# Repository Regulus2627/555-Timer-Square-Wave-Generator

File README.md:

555 Timer Square Wave Generator

This project implements an **Astable Multivibrator using the NE555 Timer IC** to generate a stable square wave. It was designed, simulated in **LTspice**, and built on a **PCB**.

Objectives

- **Frequency:** ~650 Hz  
- **Duty Cycle:** ~65%  
- **Tools Used:** LTspice + EasyEDA PCB  

## Circuit Details

The 555 timer operates in **Astable Mode**, continuously switching between HIGH and LOW.

**Components:**
- R1 = 12 kΩ  
- R2 = 6.2 kΩ  
- C2 = 0.1 µF (Timing)  
- C1 = 0.01 µF (Bypass)  
- Vcc = 5V  

## Results

| Parameter   | Theoretical | Simulation | Hardware |
|------------|------------|------------|----------|
| Frequency  | 642 Hz     | 648 Hz     | 555 Hz   |
| Duty Cycle | 65%        | 65%        | 66%      |

**Note:** Hardware variation is due to component tolerances and PCB effects.

##  Project Structure
- /docs → Report (Output waveforms & PCB photos)
- /simulation → LTspice files
- /pcb → PCB design (EasyEDA)

##  Simulation Steps
1. Open `.asc` file in LTspice  
2. Run: .tran 0 10m
3. View output waveform  

##  Team
- Nimisha Thoppil  
- Sagarika Pramod  
- Aishwarya Vaidya  
- Vaibhav Shelar  

**Guide:** Prof. Swati Patil  
Pillai College of Engineering  

## Applications

- Clock signals  
- PWM generation  
- Basic oscillators

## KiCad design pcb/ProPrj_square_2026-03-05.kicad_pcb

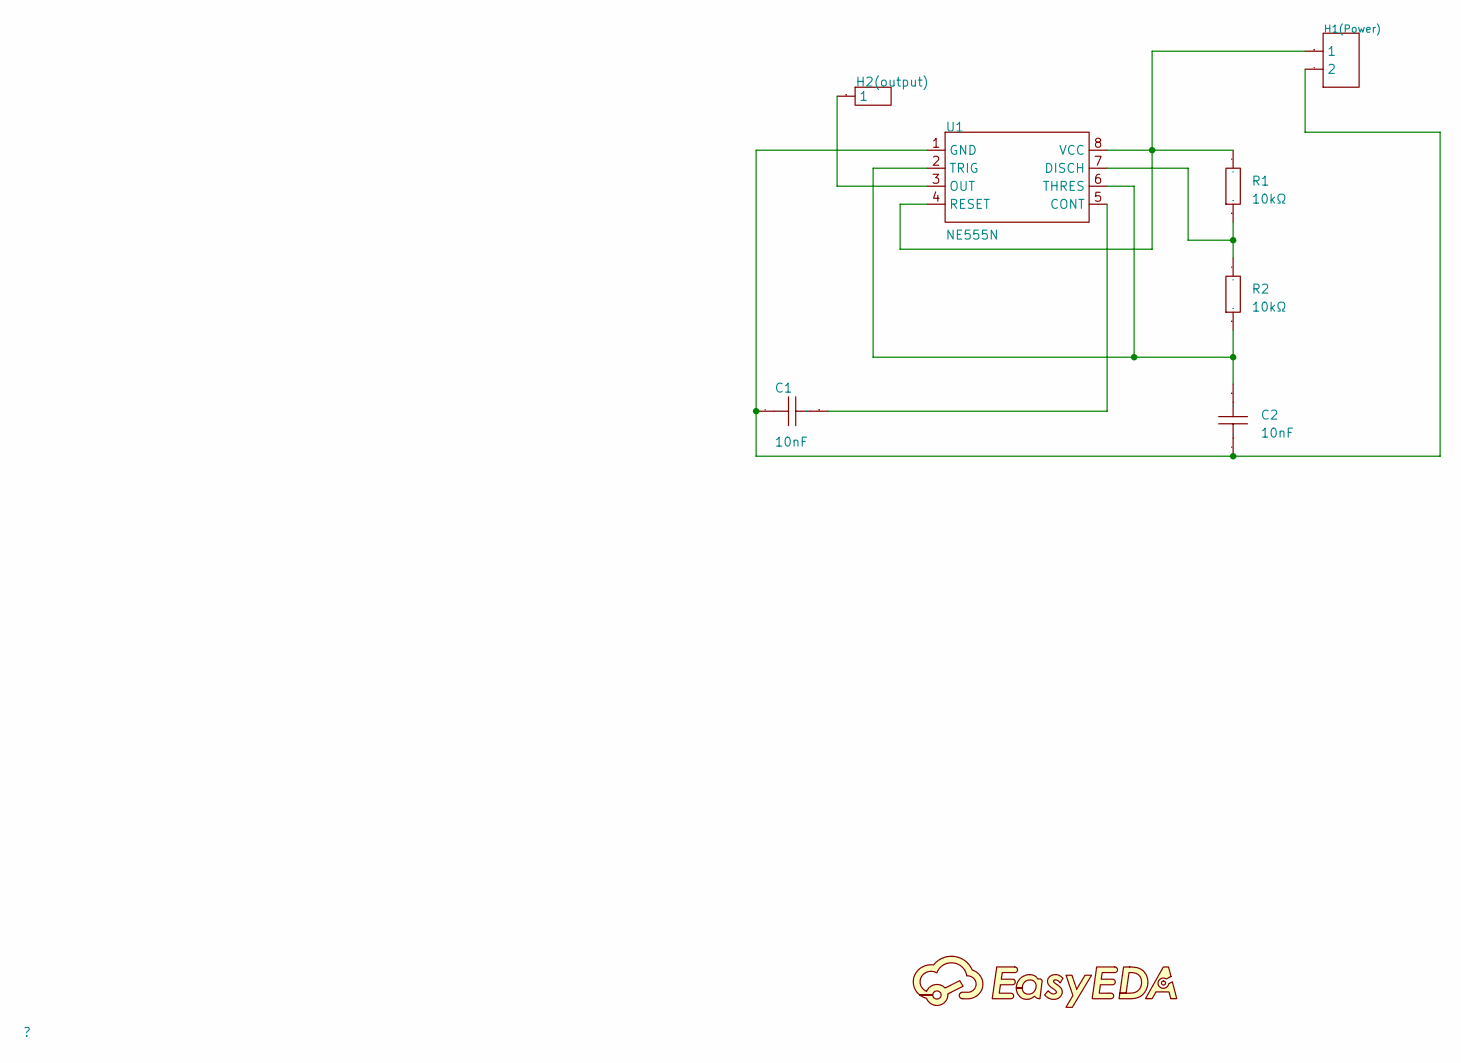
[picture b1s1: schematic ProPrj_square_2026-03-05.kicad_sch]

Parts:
C1, C2: 10nF; CAP-TH_L4.9-W3.7-P5.08-D0.5; Manufacturer Part CC4-0805-CG-50V-0.01uF-J; LCSC Part Name 10nF ±5% 50V
H1(Power): HDR-TH_2P-P2.54-V-F
H2(output): HDR-TH_1P-V-M_XKB_X4611WV-01I-C28D40
R1, R2: 10kΩ; RES-TH_BD1.8-L3.2-P7.20-D0.4
U1: NE555N; DIP-8_L9.8-W6.6-P2.54-LS7.6-BL; Manufacturer Part NE555N; LCSC Part Name 时基集成芯片

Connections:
$3N674: H1(Power).1, R1.2, U1.4 (RESET), U1.8 (VCC)
$3N891: C2.1, R2.1, U1.2 (TRIG), U1.6 (THRES)
$3N940: C1.2, C2.2, H1(Power).2, U1.1 (GND)
$3N945: C1.1, U1.5 (CONT)
$3N953: H2(output).1, U1.3 (OUT)
$3N1475: R1.1, R2.2, U1.7 (DISCH)

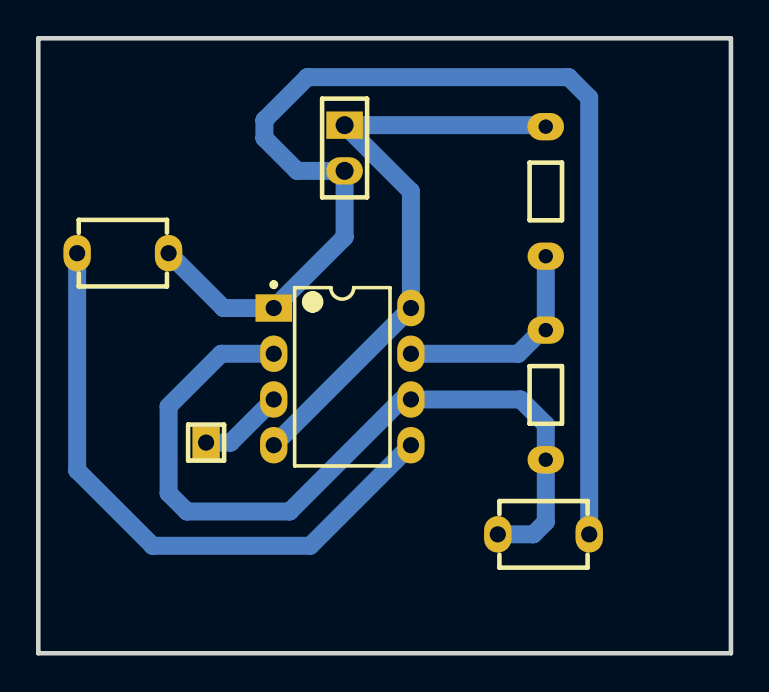
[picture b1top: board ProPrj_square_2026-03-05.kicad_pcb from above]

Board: 2 copper layers, 38.5 x 34.2 mm, 7 parts (0 on the bottom side), 6 nets.

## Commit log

2026-05-01 Update README with project details and structure
    Added project details for 555 Timer Square Wave Generator including objectives, circuit details, results, project structure, simulation steps, team members, and applications.
2026-05-01 Update README.md formatting and sections
2026-05-01 Fix formatting in project structure section of README
2026-05-01 Fix formatting in project structure section
2026-05-01 Update README with detailed project structure
    Clarified project structure and updated documentation.
